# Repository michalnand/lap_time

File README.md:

# lap_time
laser lap time measurement for robotics competitions

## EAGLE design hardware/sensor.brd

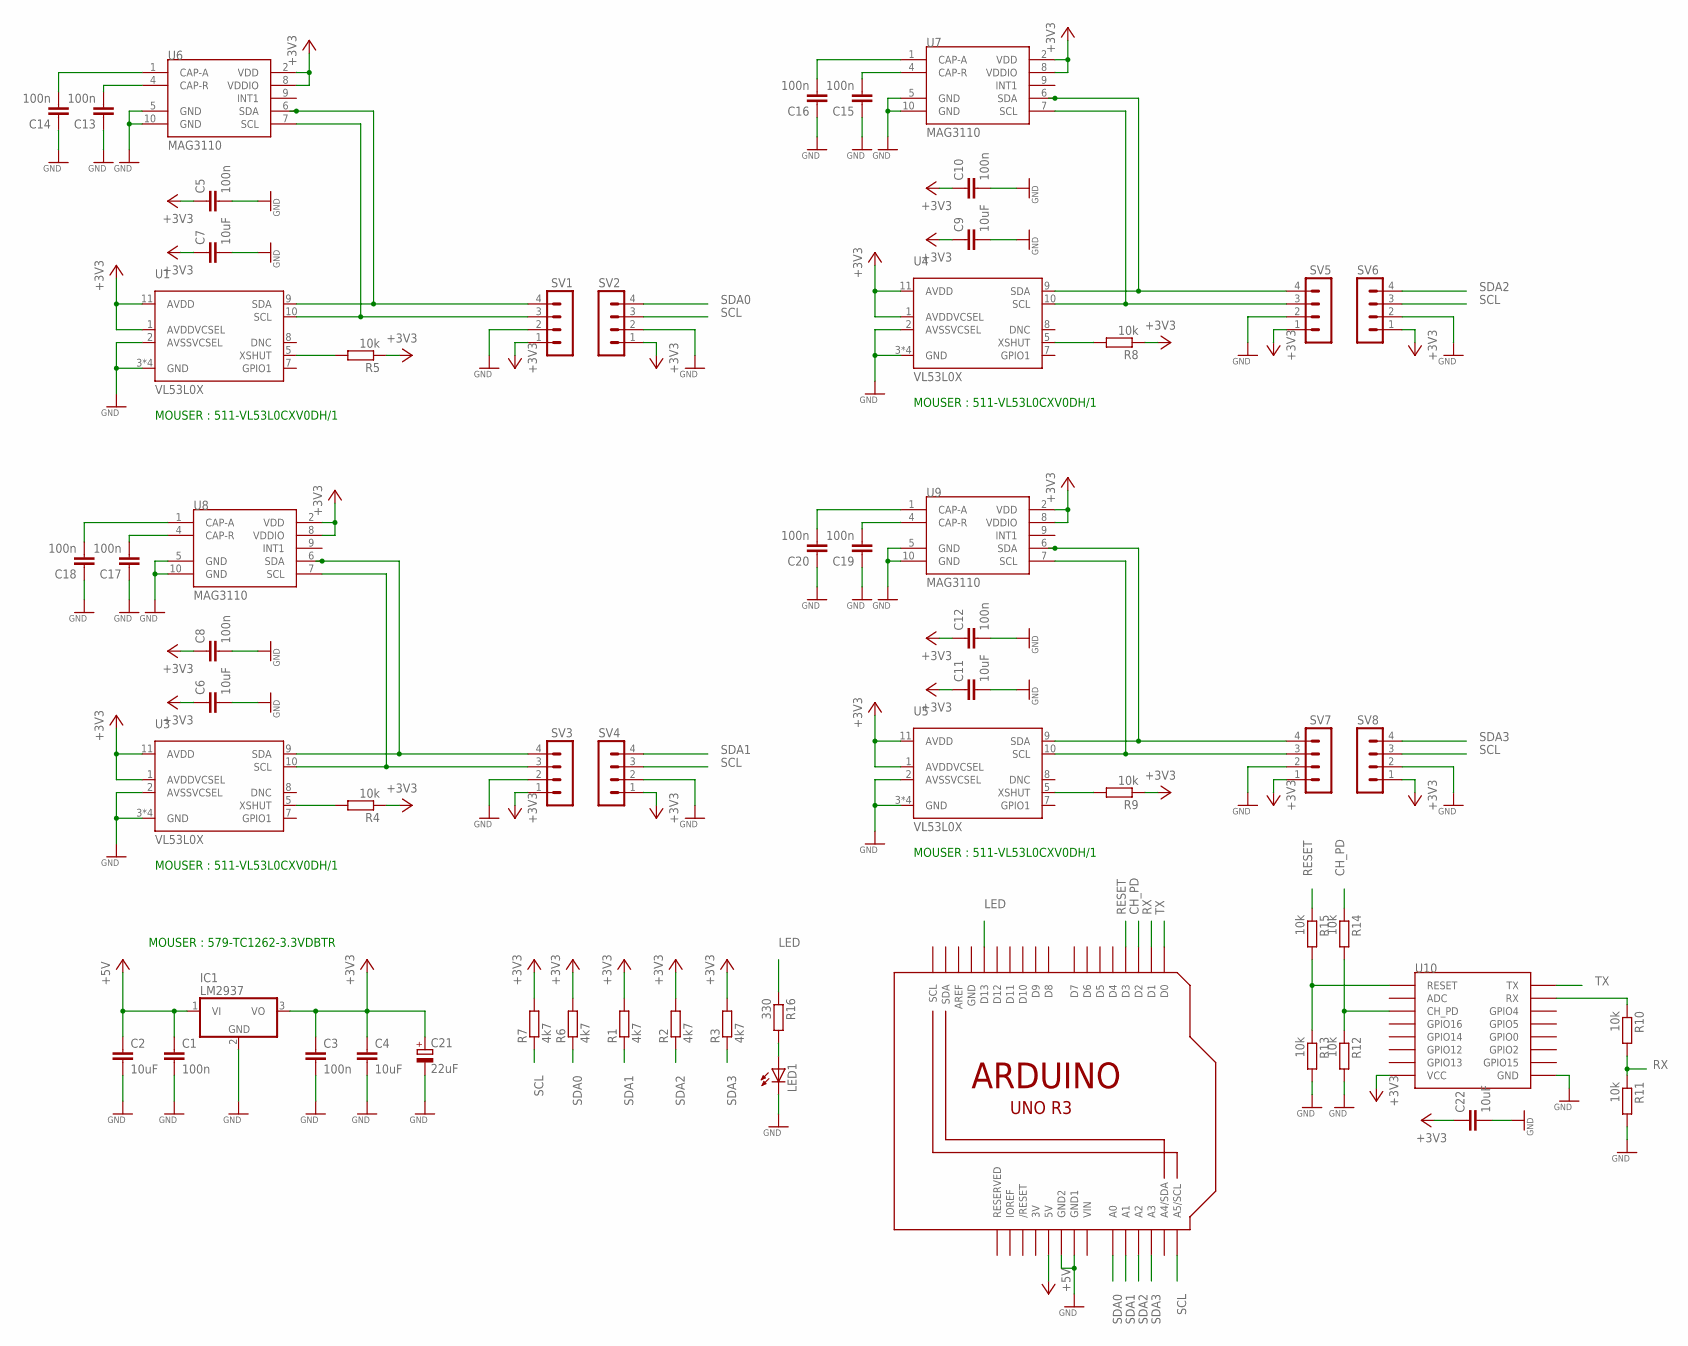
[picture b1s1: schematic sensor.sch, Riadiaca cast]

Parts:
C1, C3, C5, C8, C10, C12, C13, C14, C15, C16, C17, C18, C19, C20: 100n; C0805K
C2, C4, C6, C7, C9, C11, C22: 10uF; C0805K
C21: 22uF; 153CLV-0405
IC1: LM2937; TO263-3
LED1: LEDSML1206; SML1206
R1, R2, R3, R6, R7: 4k7; R0805
R4, R5, R8, R9, R10, R11, R12, R13, R14, R15: 10k; R0805
R16: 330; R0805
SV1, SV2, SV3, SV4, SV5, SV6, SV7, SV8: MA04-1
U1, U3, U4, U5: VL53L0X
U2: ARDUINOR3-BPLACE
U6, U7, U8, U9: MAG3110; DFN-10
U10: ESP12SMD; ESP12-SMD

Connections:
3V: U2.3V
+3V3: C3.1, C4.1, C5.1, C6.1, C7.1, C8.1, C9.1, C10.1, C11.1, C12.1, C21.+, C22.1, IC1.3 (VO), R1.2, R2.2, R3.2, R4.1, R5.1, R6.2, R7.2, R8.1, R9.1, SV1.1, SV2.1, SV3.1, SV4.1, SV5.1, SV6.1, SV7.1, SV8.1, U1.1 (AVDDVCSEL), U1.11 (AVDD), U3.1 (AVDDVCSEL), U3.11 (AVDD), U4.1 (AVDDVCSEL), U4.11 (AVDD), U5.1 (AVDDVCSEL), U5.11 (AVDD), U6.2 (VDD), U6.8 (VDDIO), U7.2 (VDD), U7.8 (VDDIO), U8.2 (VDD), U8.8 (VDDIO), U9.2 (VDD), U9.8 (VDDIO), U10.VCC
+5V: C1.1, C2.1, IC1.1 (VI), U2.5V
CH_PD: R14.1, U2.D2
GND: C1.2, C2.2, C3.2, C4.2, C5.2, C6.2, C7.2, C8.2, C9.2, C10.2, C11.2, C12.2, C13.1, C14.1, C15.1, C16.1, C17.1, C18.1, C19.1, C20.1, C21.-, C22.2, IC1.2 (GND), LED1.C, R11.2, R12.2, R13.2, SV1.2, SV2.2, SV3.2, SV4.2, SV5.2, SV6.2, SV7.2, SV8.2, U1.2 (AVSSVCSEL), U1.3 (GND), U1.4 (GND), U1.6 (GND), U1.12 (GND), U2.GND, U2.GND1, U2.GND2, U3.2 (AVSSVCSEL), U3.3 (GND), U3.4 (GND), U3.6 (GND), U3.12 (GND), U4.2 (AVSSVCSEL), U4.3 (GND), U4.4 (GND), U4.6 (GND), U4.12 (GND), U5.2 (AVSSVCSEL), U5.3 (GND), U5.4 (GND), U5.6 (GND), U5.12 (GND), U6.5 (GND), U6.10 (GND), U7.5 (GND), U7.10 (GND), U8.5 (GND), U8.10 (GND), U9.5 (GND), U9.10 (GND), U10.GND
LED: R16.1, U2.D13
unnamed: SV1.3, U1.10 (SCL), U6.7 (SCL)
unnamed: R5.2, U1.5 (XSHUT)
unnamed: SV1.4, U1.9 (SDA), U6.6 (SDA)
unnamed: R4.2, U3.5 (XSHUT)
unnamed: R10.1, U10.RXD0 (RX)
unnamed: R12.1, R14.2, U10.CH_PD
unnamed: R8.2, U4.5 (XSHUT)
unnamed: SV3.3, U3.10 (SCL), U8.7 (SCL)
unnamed: SV3.4, U3.9 (SDA), U8.6 (SDA)
unnamed: R9.2, U5.5 (XSHUT)
unnamed: LED1.A, R16.2
unnamed: C13.2, U6.4 (CAP-R)
unnamed: C14.2, U6.1 (CAP-A)
unnamed: SV5.3, U4.10 (SCL), U7.7 (SCL)
unnamed: SV5.4, U4.9 (SDA), U7.6 (SDA)
unnamed: C15.2, U7.4 (CAP-R)
unnamed: C16.2, U7.1 (CAP-A)
unnamed: C17.2, U8.4 (CAP-R)
unnamed: C18.2, U8.1 (CAP-A)
unnamed: SV7.3, U5.10 (SCL), U9.7 (SCL)
unnamed: SV7.4, U5.9 (SDA), U9.6 (SDA)
unnamed: C19.2, U9.4 (CAP-R)
unnamed: C20.2, U9.1 (CAP-A)
unnamed: R13.1, R15.2, U10.RESET
RESET: R15.1, U2.D3
RX: R10.2, R11.1, U2.D1
SCL: R7.1, SV2.3, SV4.3, SV6.3, SV8.3, U2.A5 (A5/SCL)
SDA0: R6.1, SV2.4, U2.A0
SDA1: R1.1, SV4.4, U2.A1
SDA2: R2.1, SV6.4, U2.A2
SDA3: R3.1, SV8.4, U2.A3
TX: U2.D0, U10.TXD0 (TX)
VIN: U2.VIN

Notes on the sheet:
MOUSER : 511-VL53L0CXV0DH/1
MOUSER : 579-TC1262-3.3VDBTR

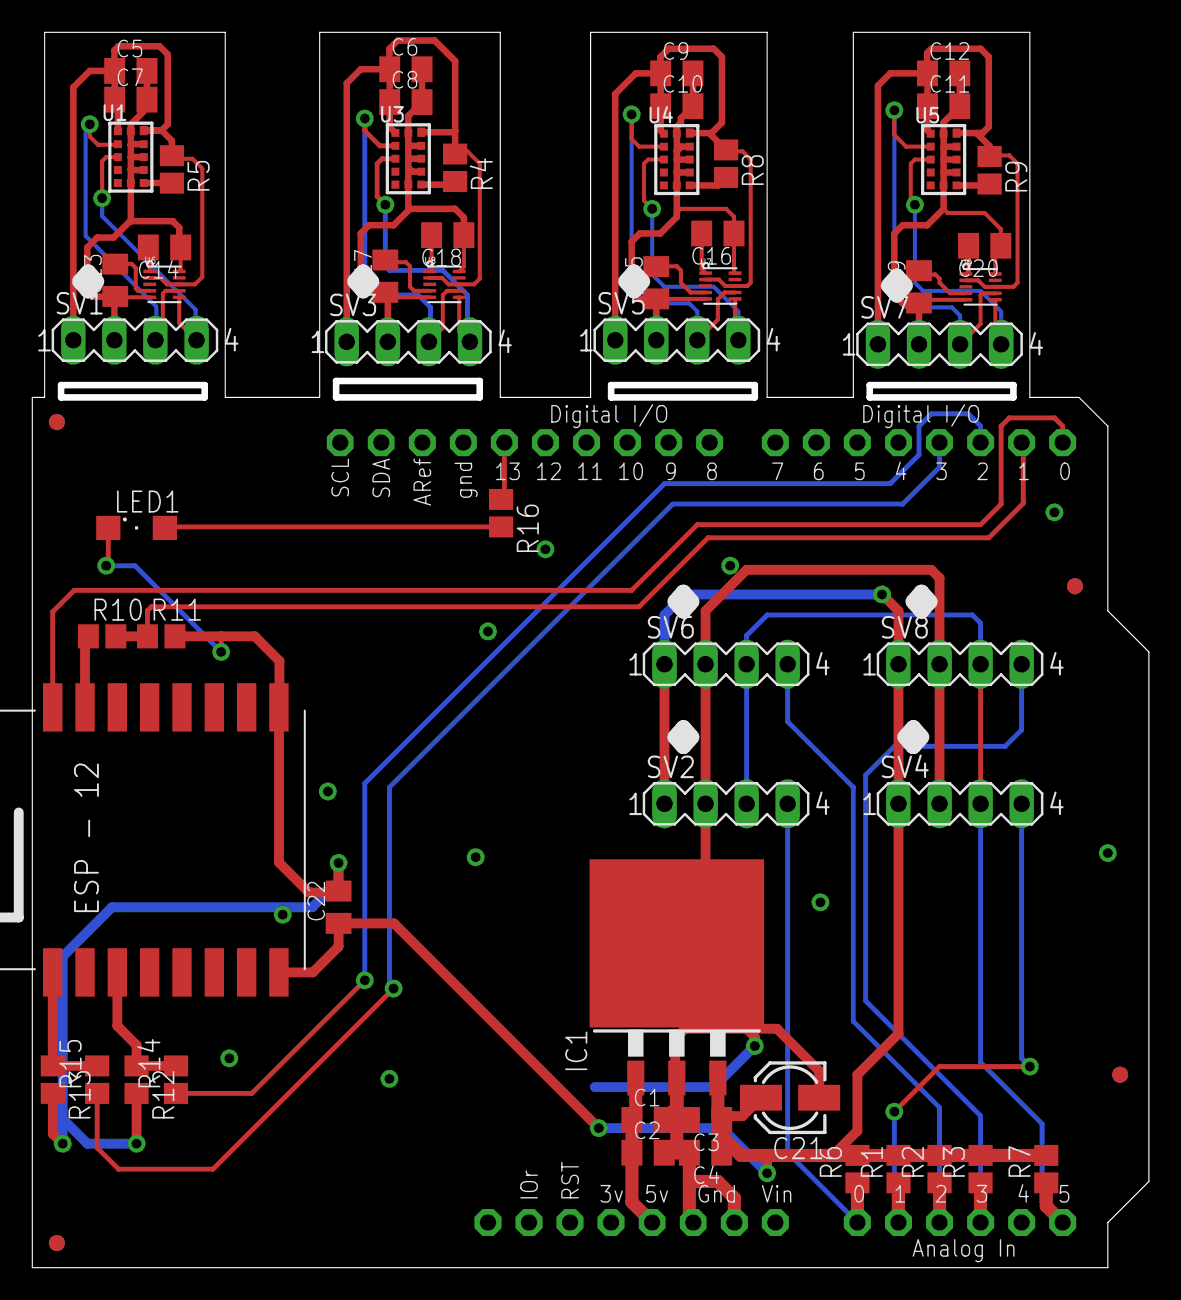
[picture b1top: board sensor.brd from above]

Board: 2 copper layers, 69.1 x 76.4 mm, 62 parts (0 on the bottom side), 37 nets.

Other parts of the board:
U$1, U$2, U$3, U$4: CIRCLE-1MM-2R

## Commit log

2017-11-27 common

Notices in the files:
parts and their libraries:
SparkFun-Sensors: Licensing: Creative Commons ShareAlike 4.0 International - https://creativecommons.org/licenses/by-sa/4.0
